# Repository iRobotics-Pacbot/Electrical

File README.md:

View this project on [CADLAB.io](https://cadlab.io/project/28443). 

﻿# Electrical

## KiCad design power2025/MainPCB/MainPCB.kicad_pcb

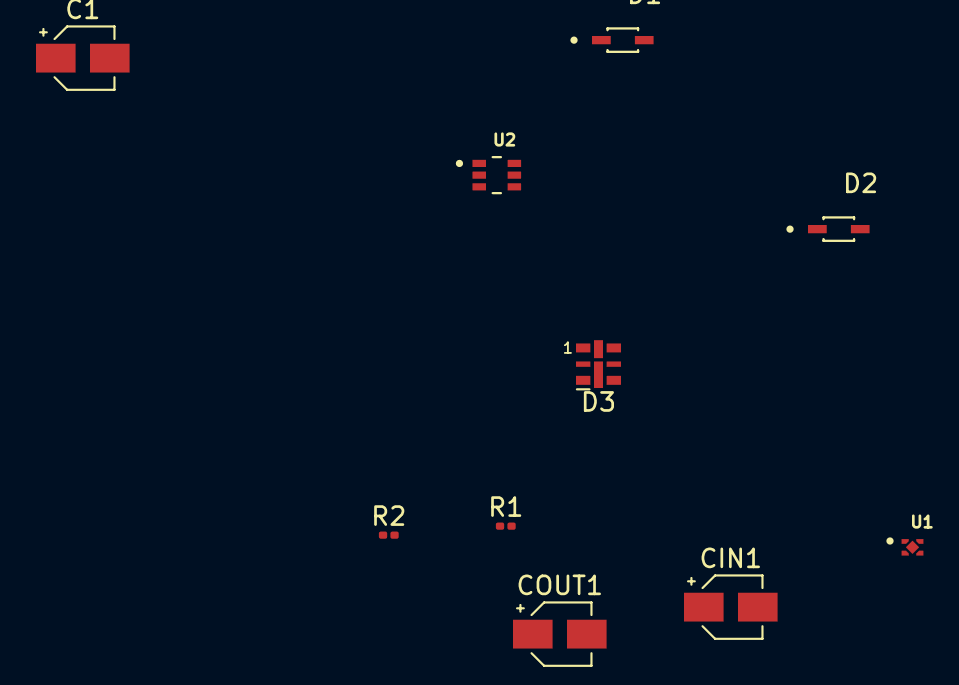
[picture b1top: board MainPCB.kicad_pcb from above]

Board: 2 copper layers, 10 parts (0 on the bottom side), 5 nets, no tracks yet.

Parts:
C1: 10uF; CP_Elec_3x5.3
CIN1: 1uF; CP_Elec_3x5.3
COUT1: 1uF; CP_Elec_3x5.3
D1, D2: D_Schottky_Filled; SOD2513X120N
D3: RED; LED-APA102-2020
R1: 100K; R_0201_0603Metric
R2: 3K3; R_0201_0603Metric
U1: NCP167BMX330TBG; VREG_NCP167BMX330TBG
U2: CJ3139K; SOP65P210X110-6N

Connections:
GND: C1.1, CIN1.2, COUT1.2, D3.1 (K), R1.1, U1.2 (GND), U1.5 (EPAD)
unnamed: C1.2, D1.1 (K), D2.2 (A), R1.2, R2.2
unnamed: CIN1.1, D2.1 (K), U1.3 (EN), U1.4 (IN)
unnamed: D3.2 (A), R2.1
unnamed: COUT1.1, U1.1 (OUT)

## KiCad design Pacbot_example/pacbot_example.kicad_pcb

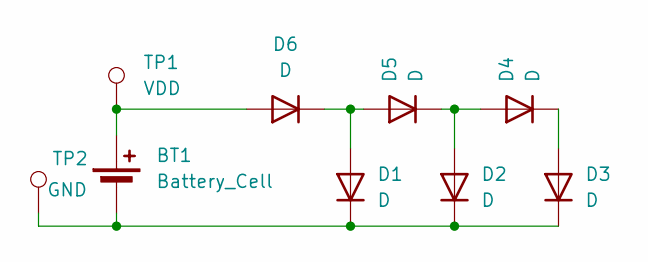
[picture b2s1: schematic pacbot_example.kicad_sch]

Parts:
BT1: Battery_Cell; BatteryHolder_LINX_BAT-HLD-012-SMT
D1, D2, D3, D4, D5, D6: D; D_0805_2012Metric
TP1: VDD; PinHeader_1x01_P2.54mm_Vertical
TP2: GND; PinHeader_1x01_P2.54mm_Vertical

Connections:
unnamed: BT1.1 (+), D6.2 (A), TP1.1
unnamed: BT1.2 (-), D1.1 (K), D2.1 (K), D3.1 (K), TP2.1
unnamed: D1.2 (A), D5.2 (A), D6.1 (K)
unnamed: D2.2 (A), D4.2 (A), D5.1 (K)
unnamed: D3.2 (A), D4.1 (K)

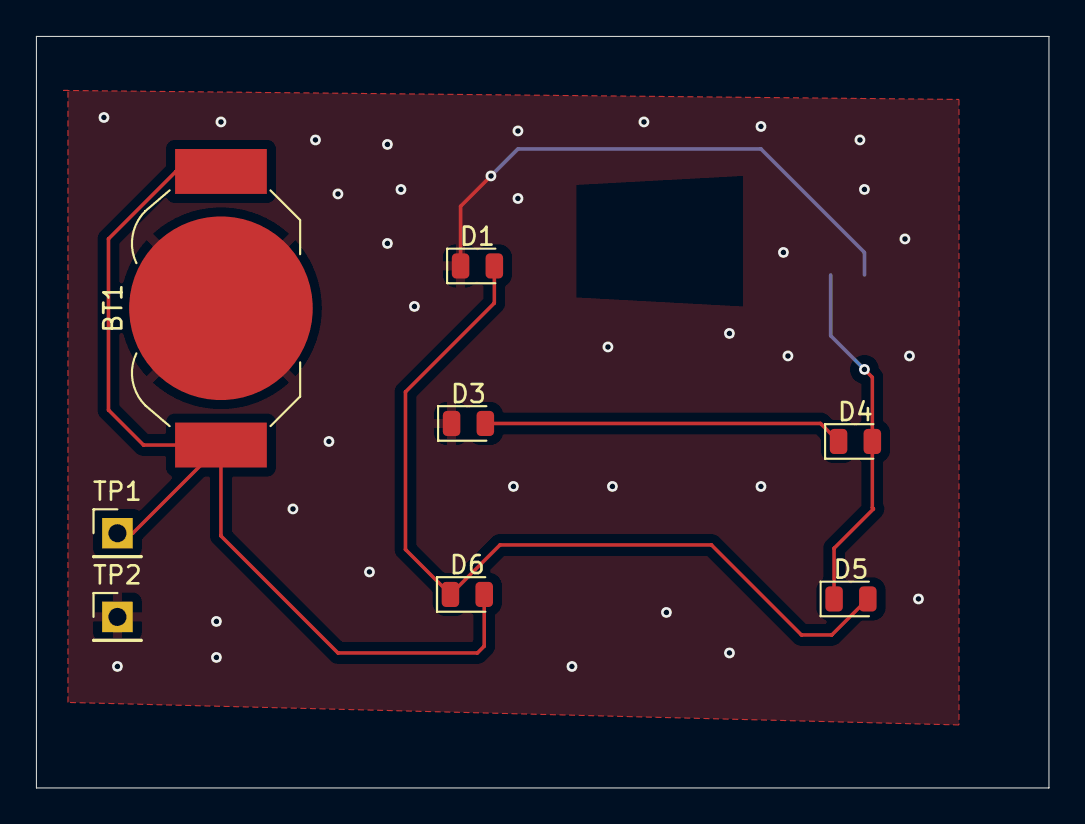
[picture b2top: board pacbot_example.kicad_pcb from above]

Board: 2 copper layers, 56.2 x 41.8 mm, 9 parts (1 on the bottom side), 5 nets.

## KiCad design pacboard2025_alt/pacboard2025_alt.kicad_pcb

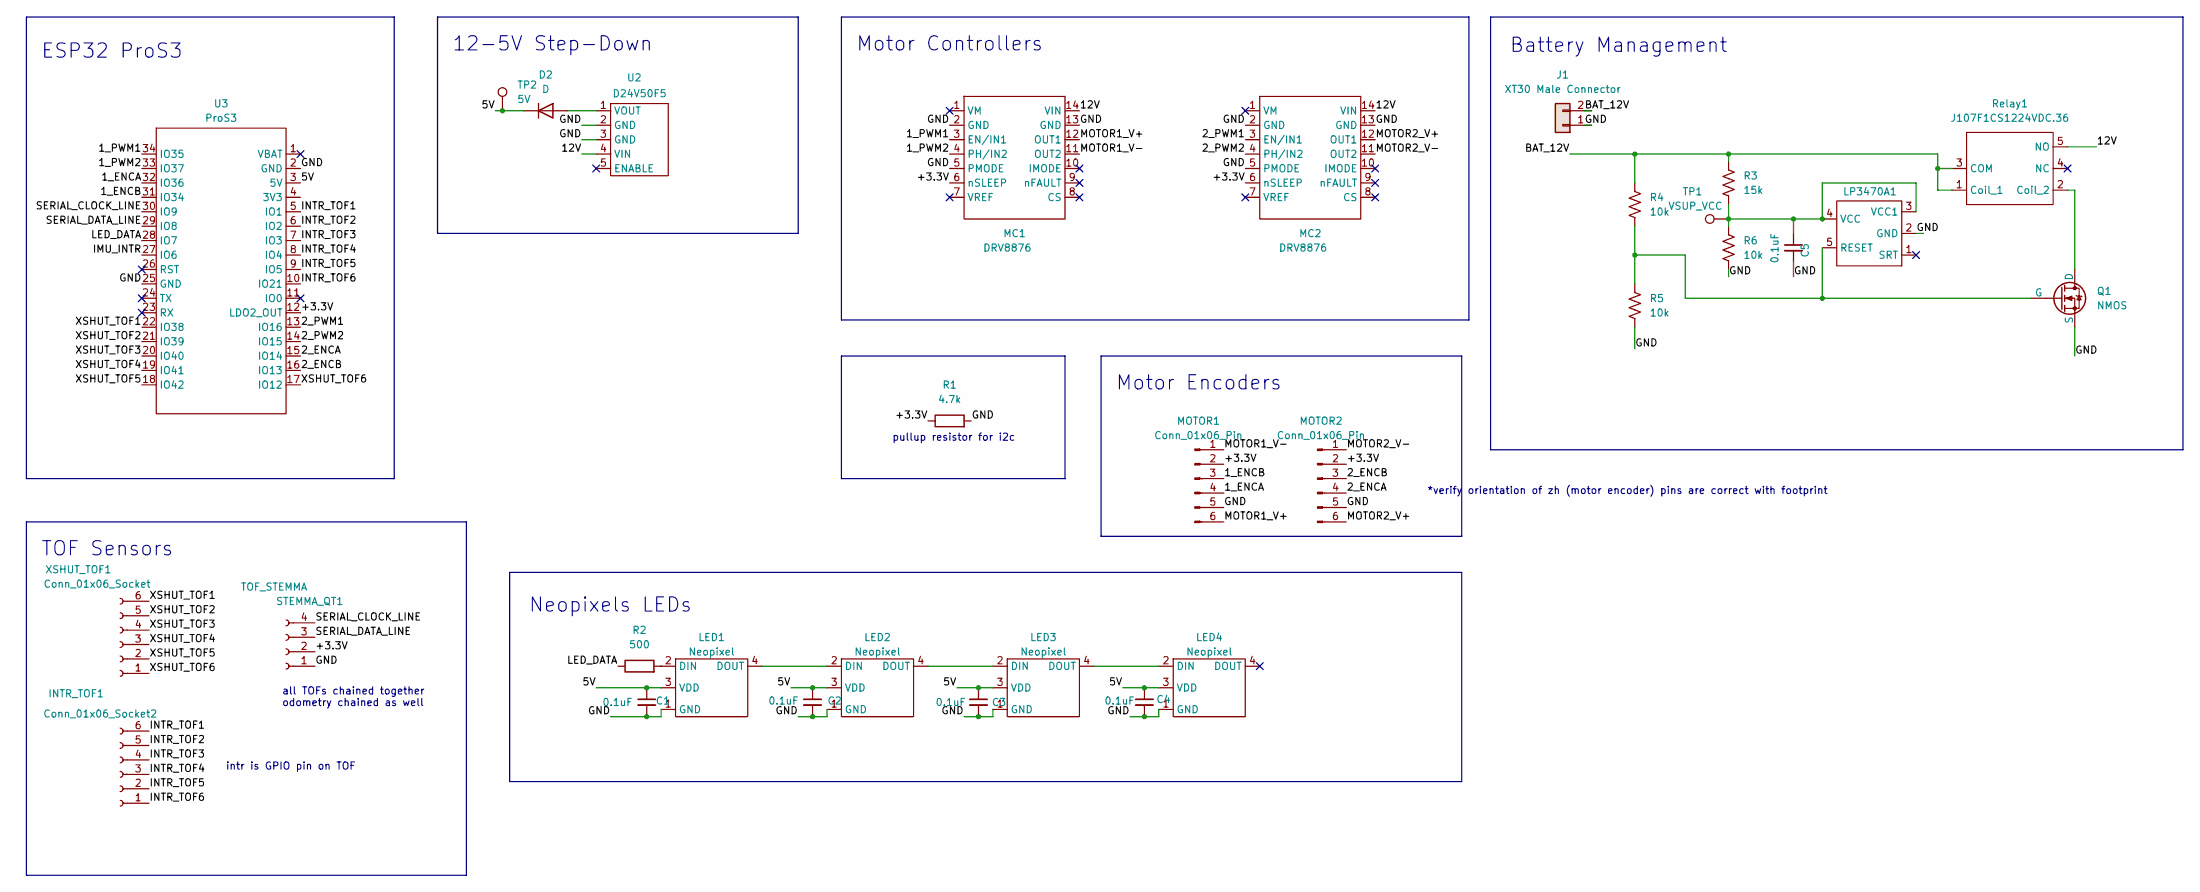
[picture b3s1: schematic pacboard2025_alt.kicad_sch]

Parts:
C1, C2, C3, C4, C5: 0.1uF; C_0805_2012Metric_Pad1.18x1.45mm_HandSolder
D2: D; D_SMB
INTR_TOF1: Conn_01x06_Socket2; PinHeader_1x06_P2.54mm_Vertical
J1: XT30 Male Connector; AMASS_XT30U-M_1x02_P5.0mm_Vertical
LED1, LED2, LED3, LED4: Neopixel; Neopixels 5050
LP3470A1: SOT-23-5
MC1, MC2: DRV8876
MOTOR1, MOTOR2: Conn_01x06_Pin; ZH1.5-6
Q1: NMOS; SOT-23
R1: 4.7k; R_0805_2012Metric_Pad1.20x1.40mm_HandSolder
R2: 500; R_0805_2012Metric_Pad1.20x1.40mm_HandSolder
R3: 15k; R_0805_2012Metric
R4, R5, R6: 10k; R_0805_2012Metric
Relay1: J107F1CS1224VDC.36; J107
STEMMA_QT1: TOF_STEMMA; JST_SH_SM04B-SRSS-TB_1x04-1MP_P1.00mm_Horizontal
TP1: VSUP_VCC; PinHeader_1x01_P2.54mm_Vertical
TP2: 5V; PinHeader_1x01_P2.54mm_Vertical
U2: D24V50F5; PinHeader_1x05_P2.54mm_Vertical
U3: ProS3; ProS3_TH (1)
XSHUT_TOF1: Conn_01x06_Socket; PinHeader_1x06_P2.54mm_Vertical

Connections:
/1_ENCA: MOTOR1.4, U3.32 (IO36)
/1_ENCB: MOTOR1.3, U3.31 (IO34)
/1_PWM1: MC1.3 (EN/IN1), U3.34 (IO35)
/1_PWM2: MC1.4 (PH/IN2), U3.33 (IO37)
/2_ENCA: MOTOR2.4, U3.15 (IO14)
/2_ENCB: MOTOR2.3, U3.16 (IO13)
/2_PWM1: MC2.3 (EN/IN1), U3.13 (IO16)
/2_PWM2: MC2.4 (PH/IN2), U3.14 (IO15)
/5V: C1.1, C2.1, C3.1, C4.1, D2.1 (K), LED1.3 (VDD), LED2.3 (VDD), LED3.3 (VDD), LED4.3 (VDD), TP2.1, U3.3 (5V)
/12V: MC1.14 (VIN), MC2.14 (VIN), Relay1.5 (NO), U2.4 (VIN)
/+3.3V: MC1.6 (nSLEEP), MC2.6 (nSLEEP), MOTOR1.2, MOTOR2.2, R1.1, STEMMA_QT1.2, U3.12 (LDO2_OUT)
/BAT_12V: J1.2, R3.1, R4.1, Relay1.1 (Coil_1), Relay1.3 (COM)
/GND: C1.2, C2.2, C3.2, C4.2, C5.2, J1.1, LED1.1 (GND), LED2.1 (GND), LED3.1 (GND), LED4.1 (GND), LP3470A1.2 (GND), MC1.2 (GND), MC1.5 (PMODE), MC1.13 (GND), MC2.2 (GND), MC2.5 (PMODE), MC2.13 (GND), MOTOR1.5, MOTOR2.5, Q1.2 (S), R1.2, R5.2, R6.2, STEMMA_QT1.1, U2.2 (GND), U2.3 (GND), U3.2 (GND), U3.25 (GND); also elsewhere on the board
/IMU_INTR: U3.27 (IO6)
/INTR_TOF1: INTR_TOF1.6, U3.5 (IO1)
/INTR_TOF2: INTR_TOF1.5, U3.6 (IO2)
/INTR_TOF3: INTR_TOF1.4, U3.7 (IO3)
/INTR_TOF4: INTR_TOF1.3, U3.8 (IO4)
/INTR_TOF5: INTR_TOF1.2, U3.9 (IO5)
/INTR_TOF6: INTR_TOF1.1, U3.10 (IO21)
/LED_DATA: R2.1, U3.28 (IO7)
/MOTOR1_V+: MC1.12 (OUT1), MOTOR1.6
/MOTOR1_V-: MC1.11 (OUT2), MOTOR1.1
/MOTOR2_V+: MC2.12 (OUT1), MOTOR2.6
/MOTOR2_V-: MC2.11 (OUT2), MOTOR2.1
/SERIAL_CLOCK_LINE: STEMMA_QT1.4, U3.30 (IO9)
/SERIAL_DATA_LINE: STEMMA_QT1.3, U3.29 (IO8)
/XSHUT_TOF1: U3.22 (IO38), XSHUT_TOF1.6
/XSHUT_TOF2: U3.21 (IO39), XSHUT_TOF1.5
/XSHUT_TOF3: U3.20 (IO40), XSHUT_TOF1.4
/XSHUT_TOF4: U3.19 (IO41), XSHUT_TOF1.3
/XSHUT_TOF5: U3.18 (IO42), XSHUT_TOF1.2
/XSHUT_TOF6: U3.17 (IO12), XSHUT_TOF1.1
unnamed: D2.2 (A), U2.1 (VOUT)
unnamed: LED1.2 (DIN), R2.2
unnamed: LED1.4 (DOUT), LED2.2 (DIN)
unnamed: LED2.4 (DOUT), LED3.2 (DIN)
unnamed: LED3.4 (DOUT), LED4.2 (DIN)
unnamed: LP3470A1.5 (RESET), Q1.1 (G), R4.2, R5.1
unnamed: C5.1, LP3470A1.3 (VCC1), LP3470A1.4 (VCC), R3.2, R6.1, TP1.1
unnamed: Q1.3 (D), Relay1.2 (Coil_2)

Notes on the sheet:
ESP32 ProS3
pullup resistor for i2c
intr is GPIO pin on TOF
Motor Encoders
all TOFs chained together odometry chained as well
12-5V Step-Down
Battery Management
*verify orientation of zh (motor encoder) pins are correct with footprint
TOF Sensors
Motor Controllers
Neopixels LEDs

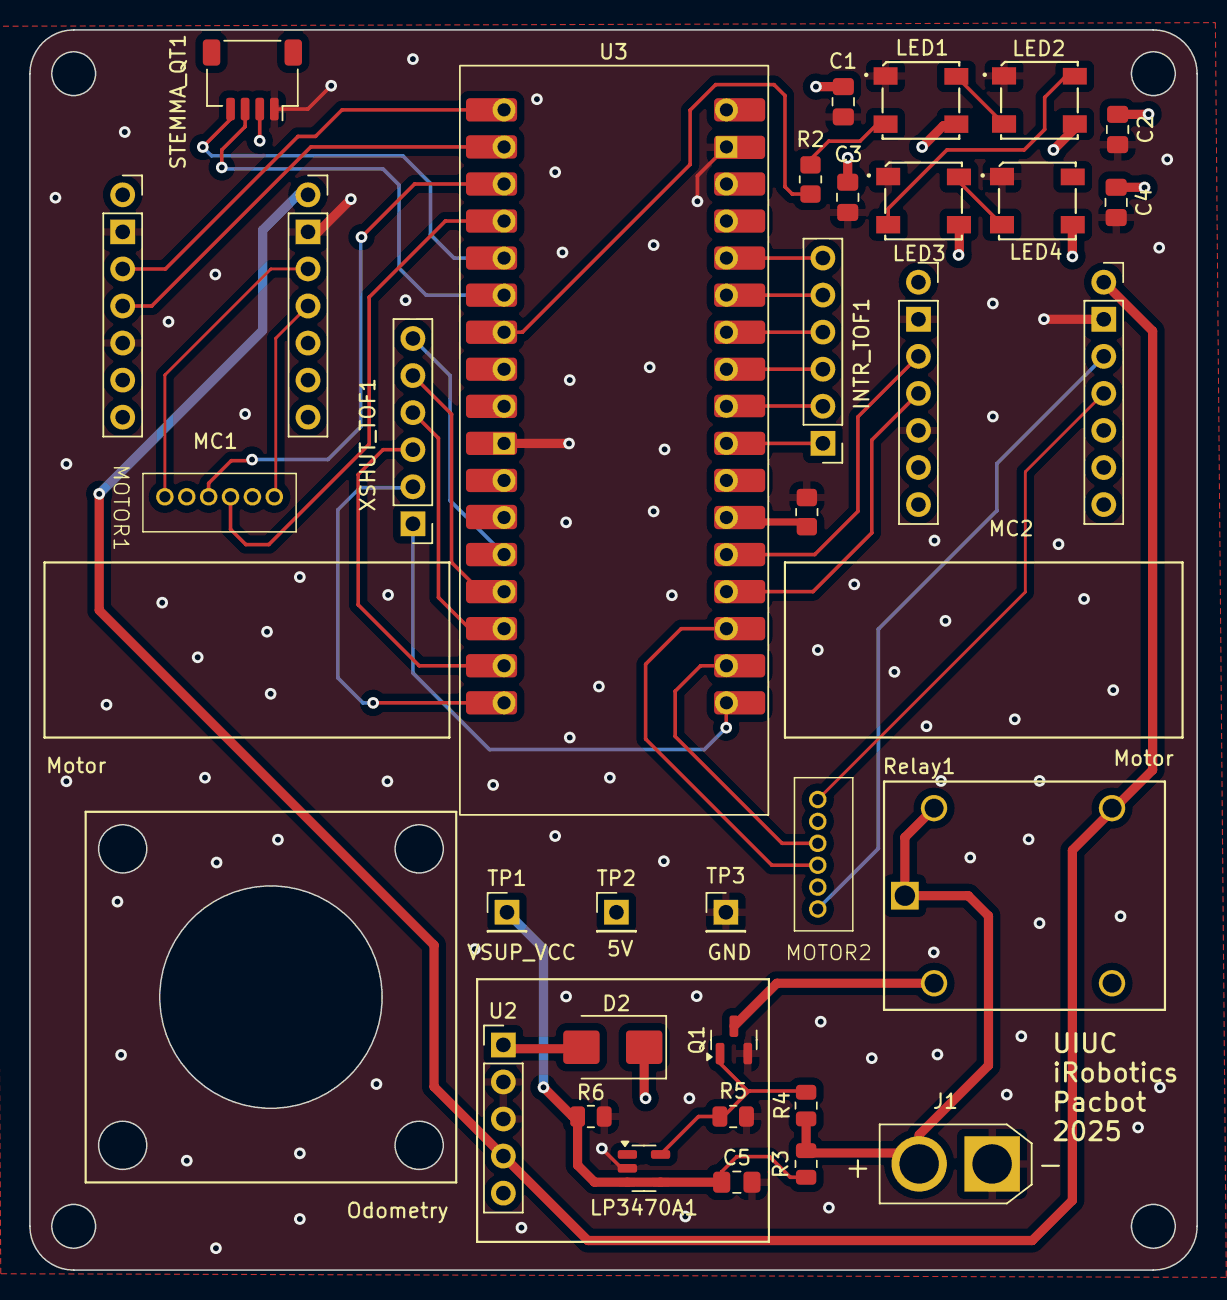
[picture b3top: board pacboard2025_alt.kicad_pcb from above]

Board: 4 copper layers, 80.0 x 85.0 mm, 32 parts (0 on the bottom side), 40 nets.

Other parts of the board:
TP3: GND; PinHeader_1x01_P2.54mm_Vertical

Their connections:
/GND: TP3.1; also elsewhere on the board

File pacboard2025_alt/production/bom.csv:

Designator,Footprint,Quantity,Value,LCSC Part #
"C1, C2, C3, C4, C5",805,5,0.1uF,C49678
D2,D_SMB,1,D,C413465
"MOTOR1, MOTOR2",ZH1.5-6,2,Conn_01x06_Pin,C722926
Q1,SOT-23,1,NMOS,C2589
R1,805,1,4.7k,C17673
R2,805,1,500,C2828711
R3,805,1,15k,C17475
"R4, R5, R6",805,3,10k,C17414
TP1,PinHeader_1x01_P2.54mm_Vertical,1,VSUP_VCC,C2906762
TP2,PinHeader_1x01_P2.54mm_Vertical,1,5V,C2906762
TP3,PinHeader_1x01_P2.54mm_Vertical,1,GND,C2906762

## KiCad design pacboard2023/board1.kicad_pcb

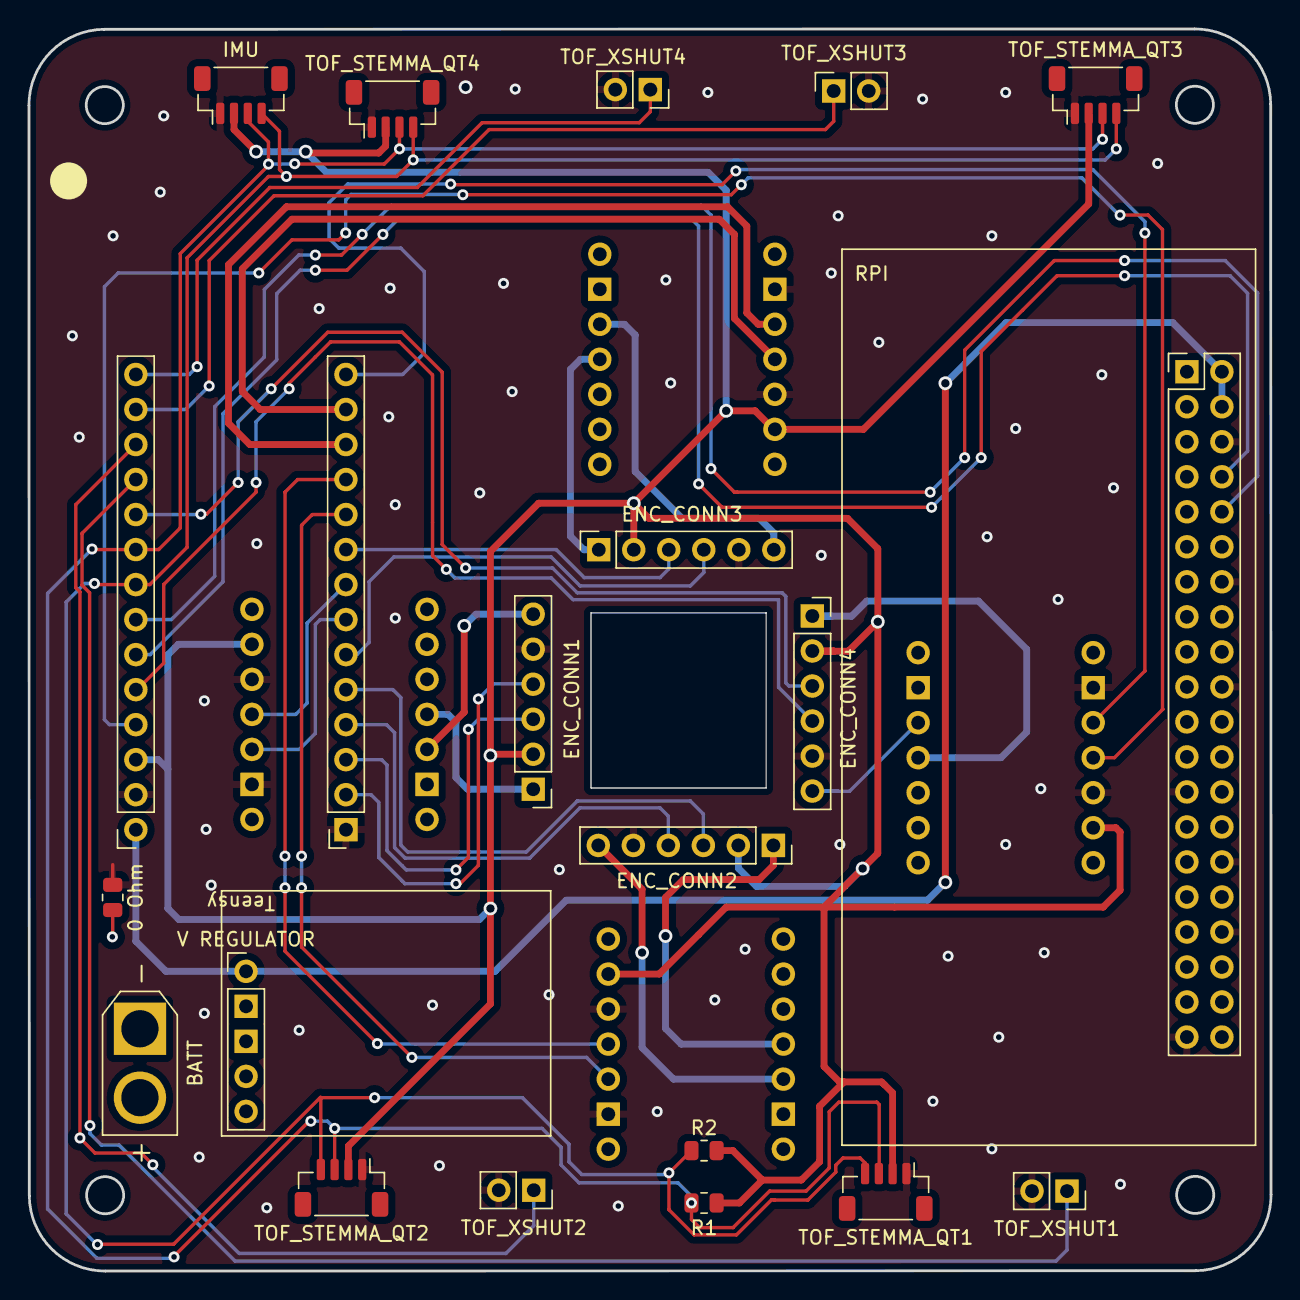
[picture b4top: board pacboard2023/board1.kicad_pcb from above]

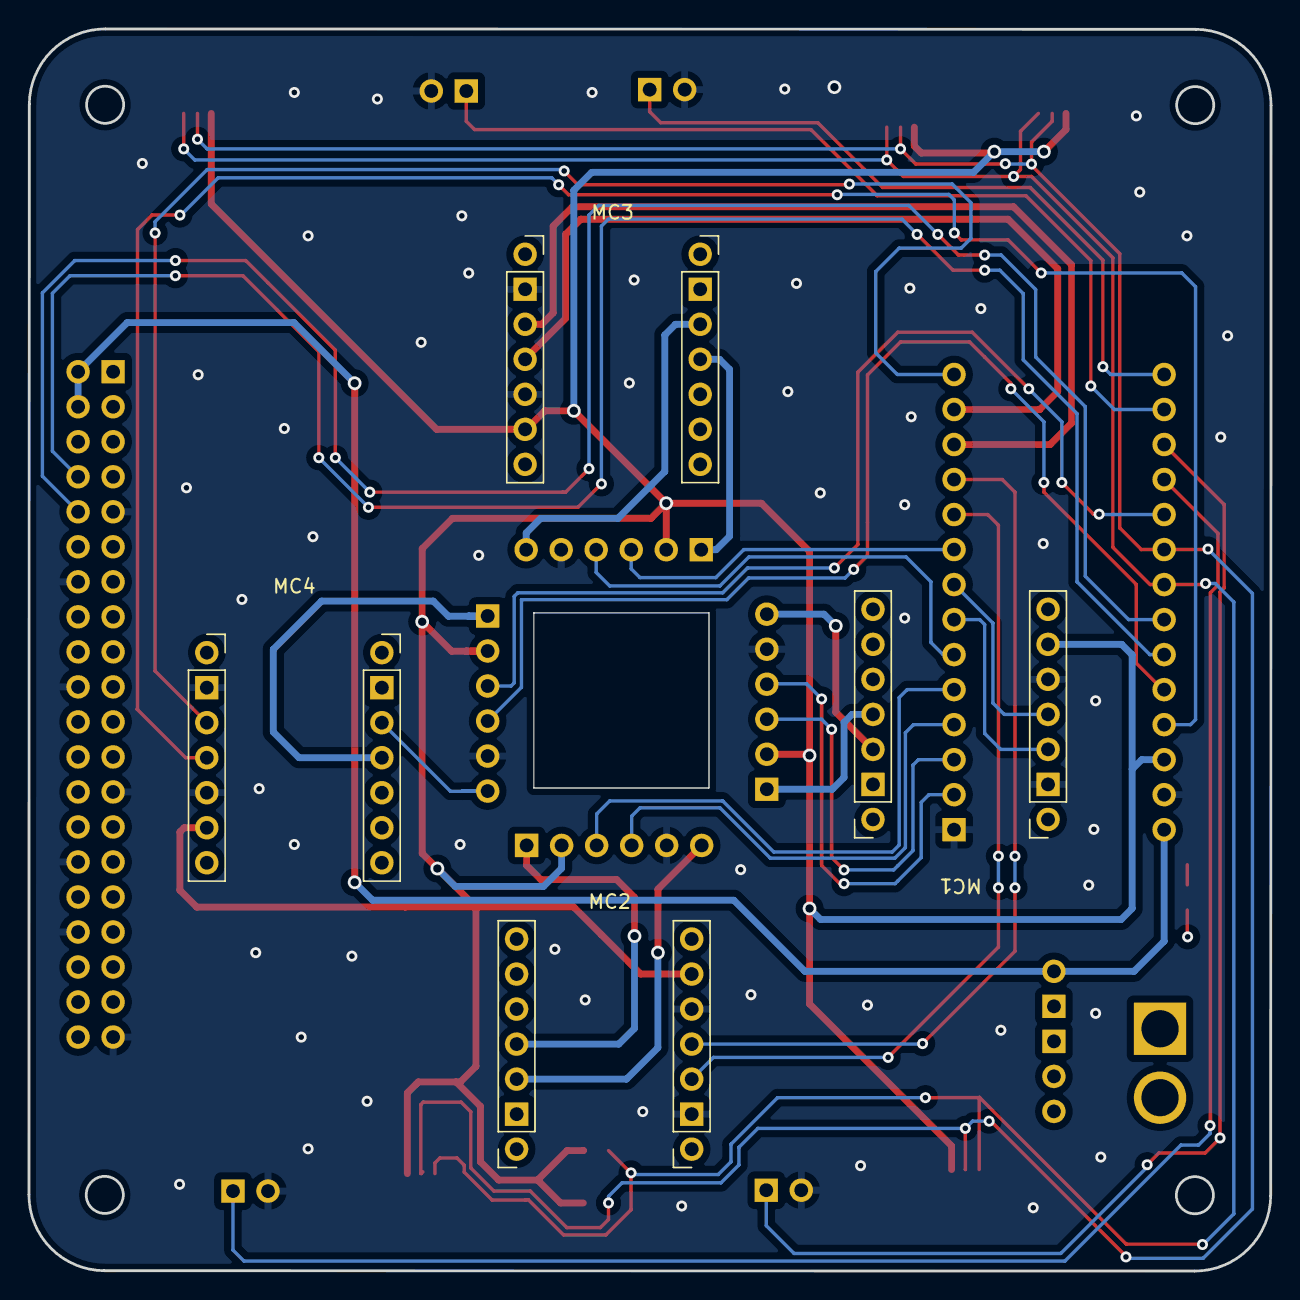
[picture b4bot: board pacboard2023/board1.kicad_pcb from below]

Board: 4 copper layers, 90.1 x 90.1 mm, 24 parts (4 on the bottom side), 37 nets.

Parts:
0 Ohm: 0 Ohms; R_0805_2012Metric
BATT: XT30 Male Connector; AMASS_XT30U-M_1x02_P5.0mm_Vertical
ENC_CONN1: Conn_01x06_Male; PinHeader_1x06_P2.54mm_Vertical
ENC_CONN2, ENC_CONN3, ENC_CONN4: Conn_01x06_Male; PinSocket_1x06_P2.54mm_Vertical
IMU: BNO085; JST_SH_BM04B-SRSS-TB_1x04-1MP_P1.00mm_Vertical
MC1, MC2, MC3, MC4: DRV8876
R1, R2: 4.7k; R_0805_2012Metric
RPI: Raspberry_PI_Zero_W; Raspberry Pi Zero W
TOF_STEMMA_QT1, TOF_STEMMA_QT2, TOF_STEMMA_QT3, TOF_STEMMA_QT4: Conn_01x04_Female; JST_SH_BM04B-SRSS-TB_1x04-1MP_P1.00mm_Vertical
TOF_XSHUT1, TOF_XSHUT2, TOF_XSHUT3, TOF_XSHUT4: Conn_01x02_Female; PinSocket_1x02_P2.54mm_Vertical
Teensy: Teensy_4.0; Teensy 4.0
V REGULATOR: D24V50F5; Voltage Regulator D24V50F5

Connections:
/3V3_Teensy: ENC_CONN1.2, ENC_CONN2.2, ENC_CONN3.2, ENC_CONN4.2, IMU.2 (VIN), MC1.6 (nSLEEP), MC2.6 (nSLEEP), MC3.6 (nSLEEP), MC4.6 (nSLEEP), R1.2, R2.2, TOF_STEMMA_QT1.2, TOF_STEMMA_QT2.2, TOF_STEMMA_QT3.2, TOF_STEMMA_QT4.2, Teensy.6 (3.3V)
/5V: RPI.2 (5V), RPI.4 (5V), Teensy.2 (Vin), V REGULATOR.1 (VOUT)
/12V: BATT.2, MC1.14 (VIN), MC2.14 (VIN), MC3.14 (VIN), MC4.14 (VIN), V REGULATOR.4 (VIN)
/BATTERY_GROUND: 0 Ohm.2, BATT.1, MC1.13 (GND), MC2.13 (GND), MC3.13 (GND), MC4.13 (GND), V REGULATOR.2 (GND), V REGULATOR.3 (GND)
/ENC_1_PINA: ENC_CONN1.4, Teensy.3 (0)
/ENC_1_PINB: ENC_CONN1.3, Teensy.5 (1)
/ENC_2_PINA: ENC_CONN2.4, Teensy.7 (2)
/ENC_2_PINB: ENC_CONN2.3, Teensy.9 (3)
/ENC_3_PINA: ENC_CONN3.4, Teensy.11 (4)
/ENC_3_PINB: ENC_CONN3.3, Teensy.17 (7)
/ENC_4_PINA: ENC_CONN4.4, Teensy.10 (22)
/ENC_4_PINB: ENC_CONN4.3, Teensy.20 (17)
/MC1_PWM1: MC1.3 (EN/IN1), Teensy.13 (5)
/MC1_PWM2: MC1.4 (PH/IN2), Teensy.15 (6)
/MC2_PWM1: MC2.3 (EN/IN1), Teensy.19 (8)
/MC2_PWM2: MC2.4 (PH/IN2), Teensy.21 (9)
/MC3_PWM1: MC3.3 (EN/IN1), Teensy.23 (10)
/MC3_PWM2: MC3.4 (PH/IN2), Teensy.25 (11)
/MC4_PWM1: MC4.3 (EN/IN1), Teensy.27 (12)
/MC4_PWM2: MC4.4 (PH/IN2), Teensy.8 (23)
/MOTOR_1_PIN1: ENC_CONN1.6, MC1.12 (OUT1)
/MOTOR_1_PIN2: ENC_CONN1.1, MC1.11 (OUT2)
/MOTOR_2_PIN1: ENC_CONN2.6, MC2.12 (OUT1)
/MOTOR_2_PIN2: ENC_CONN2.1, MC2.11 (OUT2)
/MOTOR_3_PIN1: ENC_CONN3.6, MC3.12 (OUT1)
/MOTOR_3_PIN2: ENC_CONN3.1, MC3.11 (OUT2)
/MOTOR_4_PIN1: ENC_CONN4.6, MC4.12 (OUT1)
/MOTOR_4_PIN2: ENC_CONN4.1, MC4.11 (OUT2)
/SCL_LINE: IMU.4 (SCL), R2.1, TOF_STEMMA_QT1.4, TOF_STEMMA_QT2.4, TOF_STEMMA_QT3.4, TOF_STEMMA_QT4.4, Teensy.16 (19)
/SDA_LINE: IMU.3 (SDA), R1.1, TOF_STEMMA_QT1.3, TOF_STEMMA_QT2.3, TOF_STEMMA_QT3.3, TOF_STEMMA_QT4.3, Teensy.18
/TOF_1_XSHUT: TOF_XSHUT1.1, Teensy.22 (16)
/TOF_2_XSHUT: TOF_XSHUT2.1, Teensy.24 (15)
/TOF_3_XSHUT: TOF_XSHUT3.1, Teensy.26 (14)
/TOF_4_XSHUT: TOF_XSHUT4.1, Teensy.28 (13)
/UART RXD (R PI): RPI.10 (GPIO_15_(RXD)), Teensy.14 (20)
/UART TXD (R PI): RPI.8 (GPIO_14_(TXD)), Teensy.12 (21)
GNDREF: 0 Ohm.1, ENC_CONN1.5, ENC_CONN2.5, ENC_CONN3.5, ENC_CONN4.5, IMU.1 (GND), MC1.2 (GND), MC1.5 (PMODE), MC2.2 (GND), MC2.5 (PMODE), MC3.2 (GND), MC3.5 (PMODE), MC4.2 (GND), MC4.5 (PMODE), RPI.6 (GND), RPI.9 (GND), RPI.14 (GND), RPI.20 (GND), RPI.25 (GND), RPI.30 (GND), RPI.34 (GND), RPI.39 (GND), TOF_STEMMA_QT1.1, TOF_STEMMA_QT2.1, TOF_STEMMA_QT3.1, TOF_STEMMA_QT4.1, TOF_XSHUT1.2, TOF_XSHUT2.2, TOF_XSHUT3.2, TOF_XSHUT4.2, Teensy.1 (GND), Teensy.4 (GND)

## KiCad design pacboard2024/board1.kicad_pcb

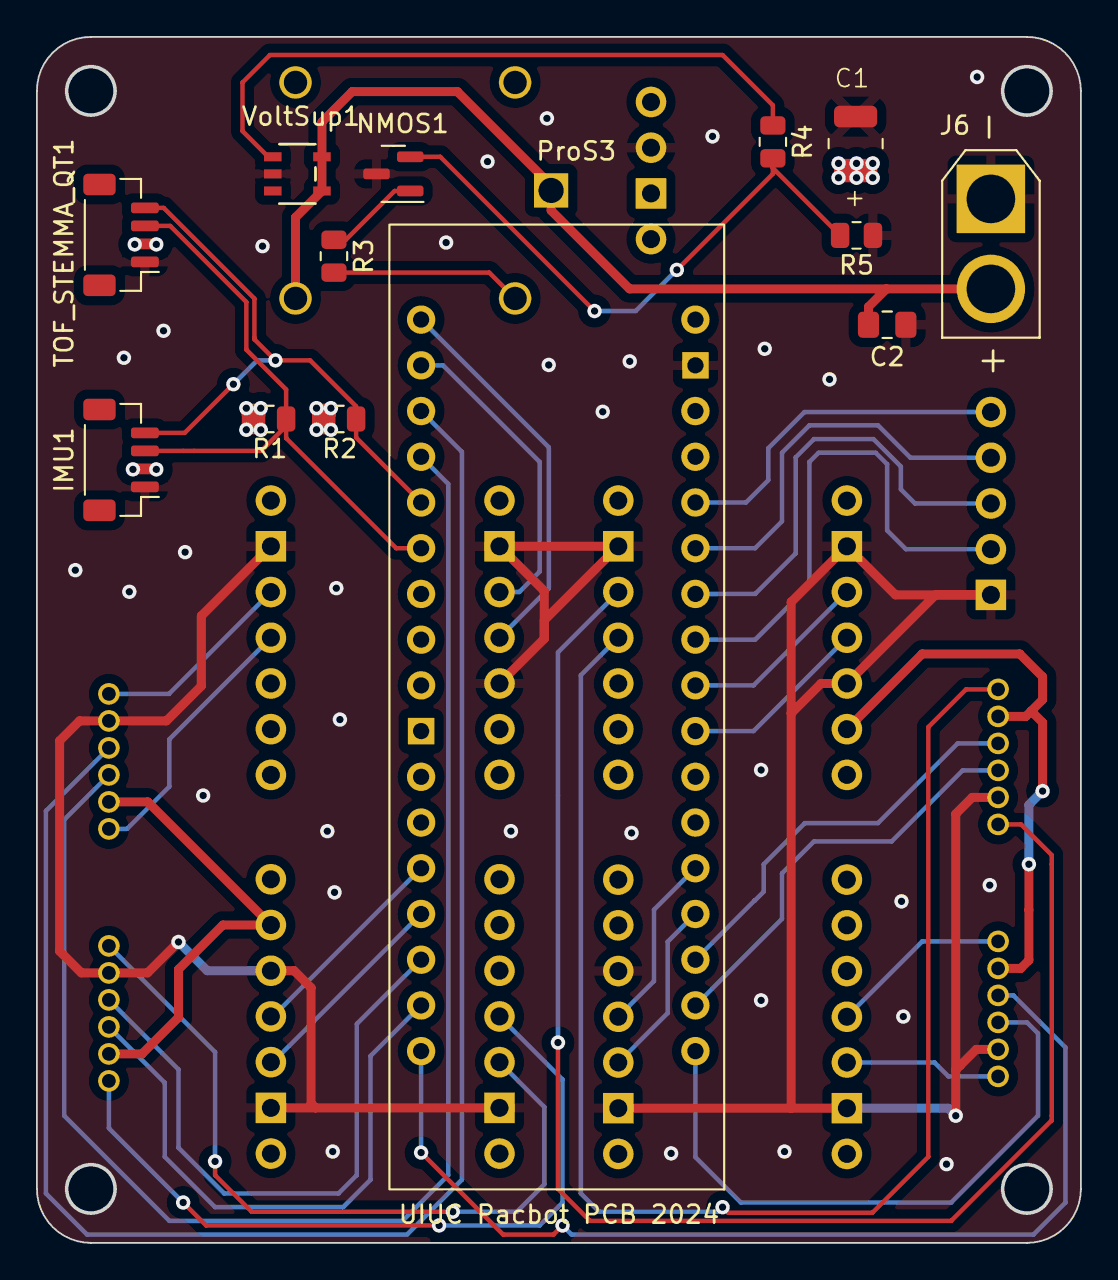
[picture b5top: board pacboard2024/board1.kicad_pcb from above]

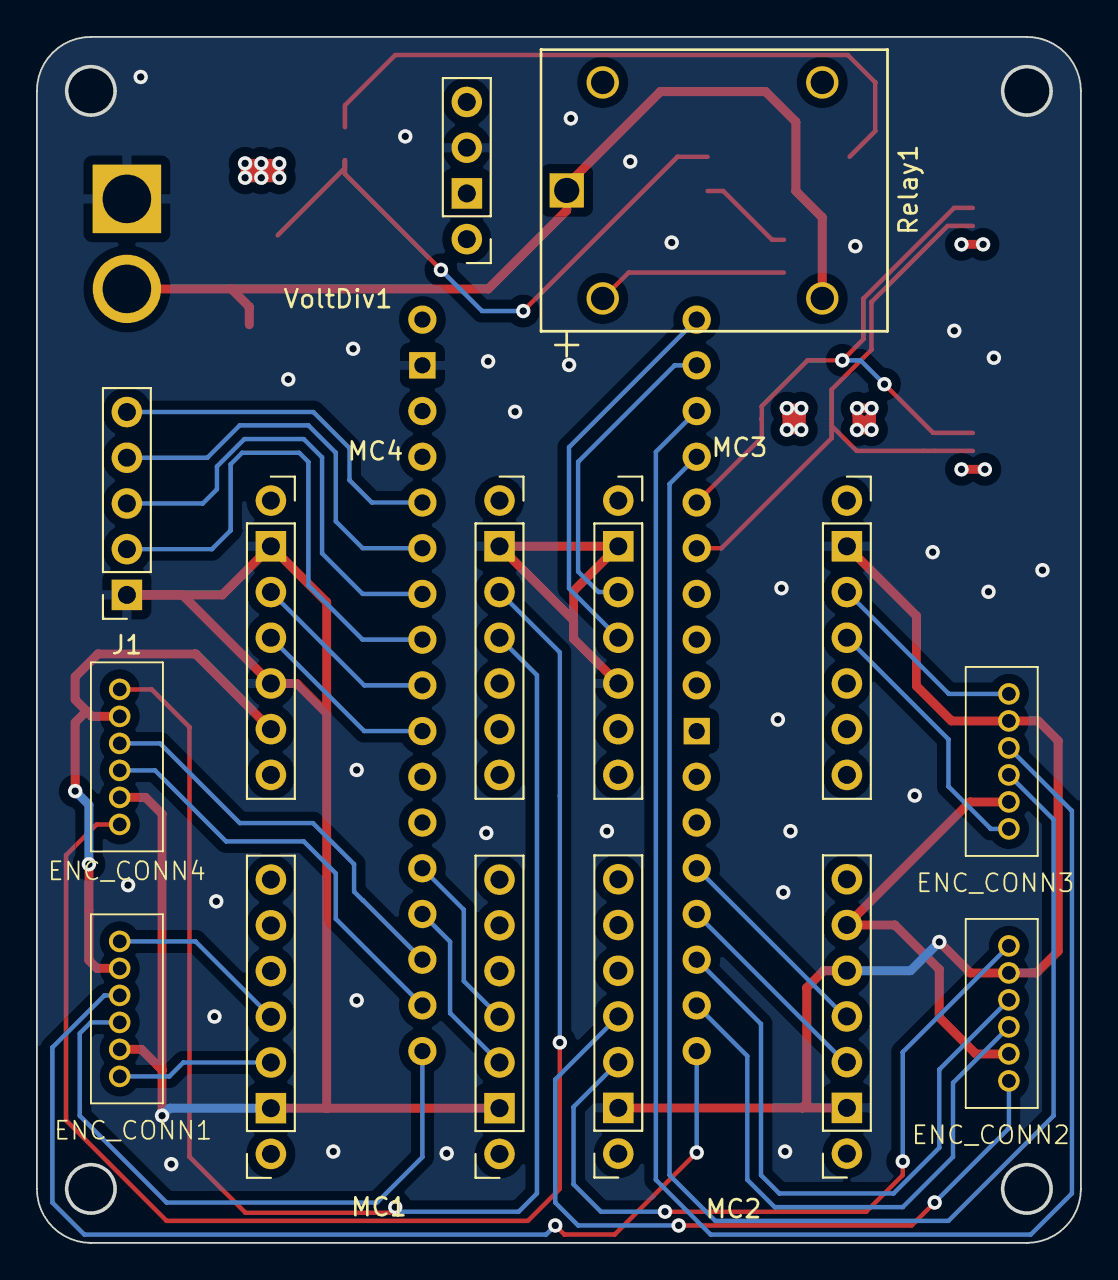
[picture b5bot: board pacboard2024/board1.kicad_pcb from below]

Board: 4 copper layers, 58.0 x 67.0 mm, 24 parts (11 on the bottom side), 38 nets.

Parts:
C1: 33uF; CA45-B-16V-33uF-K
C2: 0.1uF; C_0805_2012Metric_Pad1.18x1.45mm_HandSolder
ENC_CONN1, ENC_CONN2, ENC_CONN3, ENC_CONN4: Conn_01x06_Male; ZH1.5-6
IMU1: BNO085; JST_SH_BM04B-SRSS-TB_1x04-1MP_P1.00mm_Vertical
J1: Conn_01x05_Female; PinSocket_1x05_P2.54mm_Vertical
J6: XT30 Male Connector; AMASS_XT30U-M_1x02_P5.0mm_Vertical
MC1, MC2, MC3, MC4: DRV8876
NMOS1: Q_NMOS_DGS; SOT-23
ProS3: ProS3; ProS3_TH (1)
R1, R2: 4.7k; R_0805_2012Metric
R3: 0 Ohms; R_0805_2012Metric
R4: 1K Ohms; R_0805_2012Metric
R5: 100K Ohms; R_0805_2012Metric
Relay1: J107F1CS1224VDC.36; J107
TOF_STEMMA_QT1: Conn_01x04_Female; JST_SH_BM04B-SRSS-TB_1x04-1MP_P1.00mm_Vertical
VoltDiv1: S7V8F3
VoltSup1: TPS3847085DBVR; DBV5_TEX

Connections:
/3V3: ENC_CONN1.2, ENC_CONN2.2, ENC_CONN3.2, ENC_CONN4.2, IMU1.2 (VIN), MC1.6 (nSLEEP), MC2.6 (nSLEEP), MC3.6 (nSLEEP), MC4.6 (nSLEEP), ProS3.1 (VBAT), R1.2, R2.2, TOF_STEMMA_QT1.2, VoltDiv1.4 (VOUT)
/12V: C1.1, MC1.14 (VIN), MC2.14 (VIN), MC3.14 (VIN), MC4.14 (VIN), Relay1.5 (NO), VoltDiv1.2 (VIN)
/ENC_1_PINA: ENC_CONN1.4, ProS3.17 (IO12)
/ENC_1_PINB: ENC_CONN1.3, ProS3.18 (IO42)
/ENC_2_PINA: ENC_CONN2.4, ProS3.20 (IO40)
/ENC_2_PINB: ENC_CONN2.3, ProS3.19 (IO41)
/ENC_3_PINA: ENC_CONN3.4, ProS3.32 (IO36)
/ENC_3_PINB: ENC_CONN3.3, ProS3.31 (IO34)
/ENC_4_PINA: ENC_CONN4.4, ProS3.16 (IO13)
/ENC_4_PINB: ENC_CONN4.3, ProS3.15 (IO14)
/MC1_PWM1: MC1.3 (EN/IN1), ProS3.14 (IO15)
/MC1_PWM2: MC1.4 (PH/IN2), ProS3.13 (IO16)
/MC2_PWM1: MC2.3 (EN/IN1), ProS3.21 (IO39)
/MC2_PWM2: MC2.4 (PH/IN2), ProS3.22 (IO38)
/MC3_PWM1: MC3.3 (EN/IN1), ProS3.33 (IO37)
/MC3_PWM2: MC3.4 (PH/IN2), ProS3.34 (IO35)
/MC4_PWM1: MC4.3 (EN/IN1), ProS3.9 (IO5)
/MC4_PWM2: MC4.4 (PH/IN2), ProS3.10 (IO21)
/MOTOR_1_PIN1: ENC_CONN1.6, MC1.12 (OUT1)
/MOTOR_1_PIN2: ENC_CONN1.1, MC1.11 (OUT2)
/MOTOR_2_PIN1: ENC_CONN2.6, MC2.12 (OUT1)
/MOTOR_2_PIN2: ENC_CONN2.1, MC2.11 (OUT2)
/MOTOR_3_PIN1: ENC_CONN3.6, MC3.12 (OUT1)
/MOTOR_3_PIN2: ENC_CONN3.1, MC3.11 (OUT2)
/MOTOR_4_PIN1: ENC_CONN4.6, MC4.12 (OUT1)
/MOTOR_4_PIN2: ENC_CONN4.1, MC4.11 (OUT2)
/SCL_LINE: IMU1.4 (SCL), ProS3.30 (IO9), R2.1, TOF_STEMMA_QT1.4
/SDA_LINE: IMU1.3 (SDA), ProS3.29 (IO8), R1.1, TOF_STEMMA_QT1.3
/TOF_1_XSHUT: J1.5, ProS3.5 (IO1)
/TOF_2_XSHUT: J1.4, ProS3.6 (IO2)
/TOF_3_XSHUT: J1.3, ProS3.7 (IO3)
/TOF_4_XSHUT: J1.2, ProS3.8 (IO4)
GNDREF: C1.2, C2.2, ENC_CONN1.5, ENC_CONN2.5, ENC_CONN3.5, ENC_CONN4.5, IMU1.1 (GND), J1.1, J6.1, MC1.2 (GND), MC1.5 (PMODE), MC1.13 (GND), MC2.2 (GND), MC2.5 (PMODE), MC2.13 (GND), MC3.2 (GND), MC3.5 (PMODE), MC3.13 (GND), MC4.2 (GND), MC4.5 (PMODE), MC4.13 (GND), NMOS1.3 (S), ProS3.2 (GND), R5.1, TOF_STEMMA_QT1.1, VoltDiv1.3 (GND), VoltSup1.2 (GND)
unnamed: C2.1, J6.2, Relay1.1 (Coil_1), Relay1.3 (COM), VoltSup1.4 (*MR), VoltSup1.5 (VCC)
unnamed: NMOS1.1 (D), R3.1
unnamed: NMOS1.2 (G), R4.2, R5.2
unnamed: R3.2, Relay1.2 (Coil_2)
unnamed: R4.1, VoltSup1.1 (*RESET)

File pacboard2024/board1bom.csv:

"Id";"Designator";"Footprint";"Quantity";"Designation";"Supplier and ref";
1;"Relay1";"J107";1;"J107F1CS1224VDC.36";;;
2;"R5";"R_0805_2012Metric";1;"100K Ohms";;;
3;"NMOS1";"SOT-23";1;"Q_NMOS_DGS";;;
4;"R3";"R_0805_2012Metric";1;"0 Ohms";;;
5;"C1";"CA45-B-16V-33uF-K";1;"33uF";;;
6;"IMU1";"JST_SH_BM04B-SRSS-TB_1x04-1MP_P1.00mm_Vertical";1;"BNO085";;;
7;"TP-,TP+";"PinHeader_1x01_P2.54mm_Vertical";2;"TestPoint";;;
8;"R4";"R_0805_2012Metric";1;"1K Ohms";;;
9;"J6";"AMASS_XT30U-M_1x02_P5.0mm_Vertical";1;"XT30 Male Connector";;;
10;"R1,R2";"R_0805_2012Metric";2;"4.7k";;;
11;"VoltSup1";"DBV5_TEX";1;"TPS3847085DBVR";;;
12;"TOF_STEMMA_QT1";"JST_SH_BM04B-SRSS-TB_1x04-1MP_P1.00mm_Vertical";1;"Conn_01x04_Female";;;
13;"ProS3";"ProS3_TH (1)";1;"ProS3";;;
14;"C2";"C_0805_2012Metric_Pad1.18x1.45mm_HandSolder";1;"0.1uF";;;
15;"J1";"PinSocket_1x05_P2.54mm_Vertical";1;"Conn_01x05_Female";;;
16;"MC3,MC2,MC1,MC4";"DRV8876";4;"DRV8876";;;
17;"ENC_CONN2,ENC_CONN3,ENC_CONN4,ENC_CONN1";"ZH1.5-6";4;"Conn_01x06_Male";;;
18;"VoltDiv1";"S7V8F3";1;"~";;;

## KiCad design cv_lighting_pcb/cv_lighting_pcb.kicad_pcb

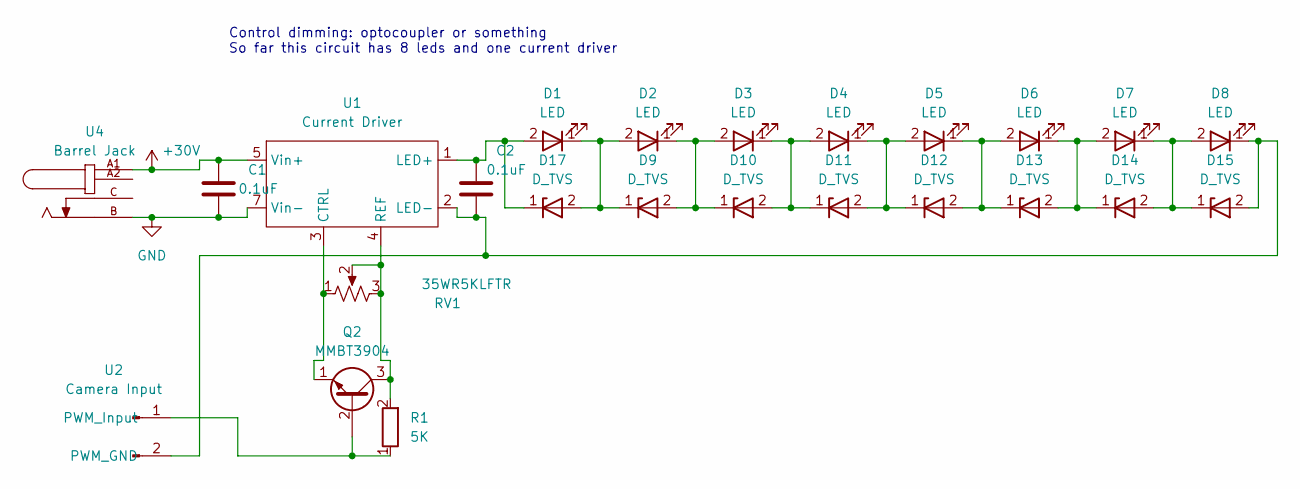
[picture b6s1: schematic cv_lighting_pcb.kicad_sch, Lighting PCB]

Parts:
C1, C2: 0.1uF; C_0805_2012Metric_Pad1.18x1.45mm_HandSolder
D1, D2, D3, D4, D5, D6, D7, D8: LED; LED_SFH4715AS
D9, D10, D11, D12, D13, D14, D15, D17: D_TVS; D3V3M1U2S9-7
Q2: MMBT3904
R1: 5K; R_0805_2012Metric_Pad1.20x1.40mm_HandSolder
RV1: 35WR5KLFTR
U1: Current Driver; 3021_Buckpuck
U2: Camera Input; PinSocket_1x02_P2.54mm_Vertical_SMD_Pin1Left
U4: Barrel Jack; TENSILITY_54-00164

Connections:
+30V: C1.1, U1.5 (Vin+), U4.A1
GND: C1.2, U1.7 (Vin-), U4.B
unnamed: C2.1, D1.2 (A), D17.1 (K), U1.1 (LED+)
unnamed: D1.1 (K), D2.2 (A), D9.1 (K), D17.2 (A)
unnamed: D3.1 (K), D4.2 (A), D10.2 (A), D11.1 (K)
unnamed: D2.1 (K), D3.2 (A), D9.2 (A), D10.1 (K)
unnamed: D4.1 (K), D5.2 (A), D11.2 (A), D12.1 (K)
unnamed: D5.1 (K), D6.2 (A), D12.2 (A), D13.1 (K)
unnamed: D6.1 (K), D7.2 (A), D13.2 (A), D14.1 (K)
unnamed: D7.1 (K), D8.2 (A), D14.2 (A), D15.1 (K)
unnamed: C2.2, D8.1 (K), D15.2 (A), U1.2 (LED-), U2.2 (PWM_GND)
unnamed: Q2.2 (B), R1.1, U2.1 (PWM_Input)
unnamed: Q2.3 (C), R1.2, RV1.2, RV1.3, U1.4 (REF)
unnamed: Q2.1 (E), RV1.1, U1.3 (CTRL)

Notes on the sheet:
Control dimming: optocoupler or something So far this circuit has 8 leds and one current driver

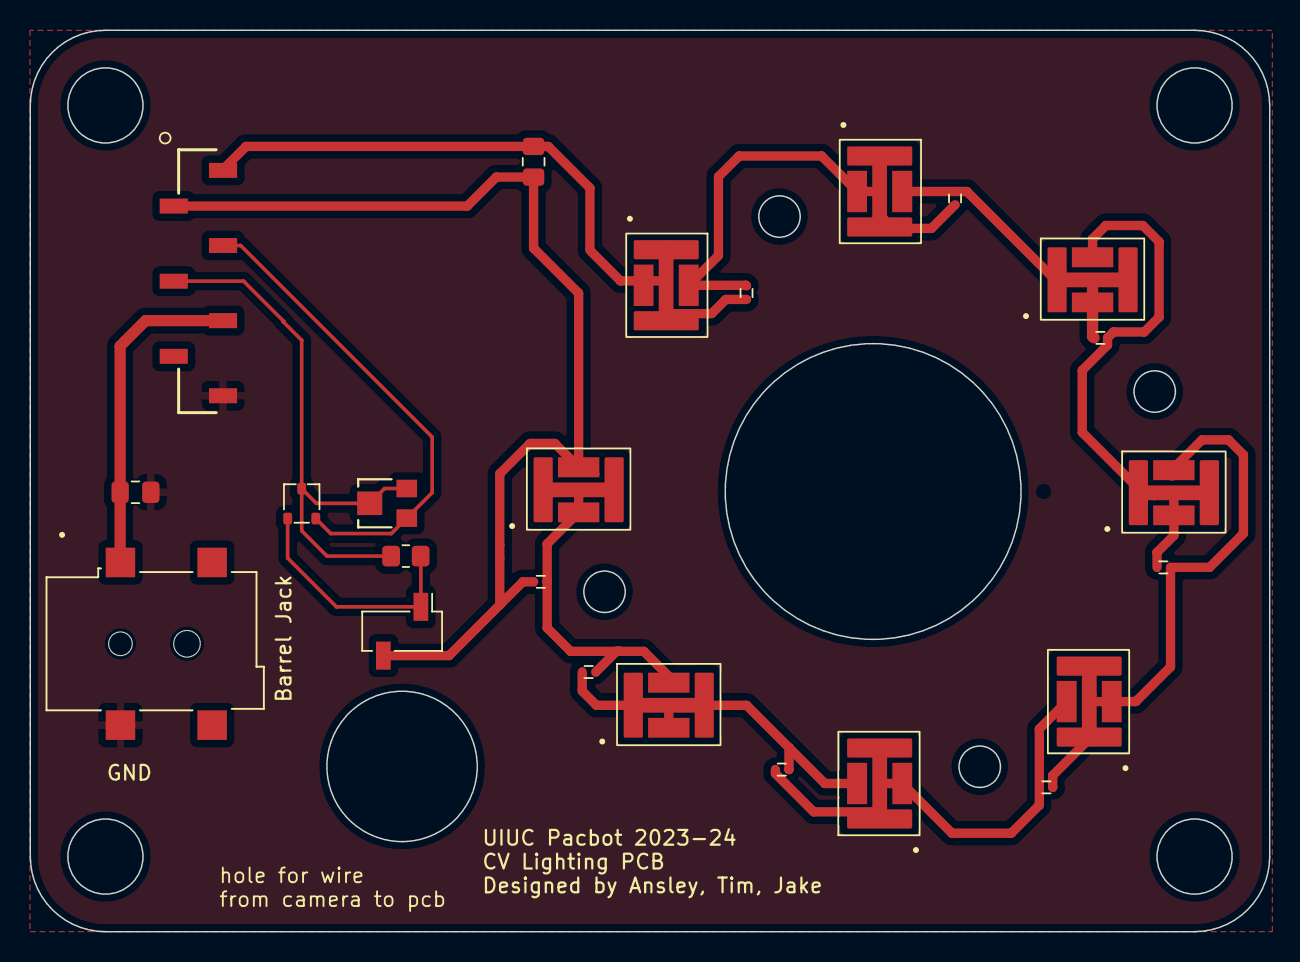
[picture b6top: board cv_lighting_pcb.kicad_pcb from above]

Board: 2 copper layers, 83.8 x 61.0 mm, 24 parts (0 on the bottom side), 14 nets.

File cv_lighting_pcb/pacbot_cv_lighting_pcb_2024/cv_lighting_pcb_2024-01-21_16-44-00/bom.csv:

Designator,Footprint,Quantity,Value,LCSC Part #
"C1, C2",0805,2,0.1uF,C49678
"D1, D2, D3, D4, D5, D6, D7, D8",LED_SFH4715AS,8,LED,C2880156
"D10, D11, D12, D13, D14, D15, D17, D9",D3V3M1U2S9-7,8,D_TVS,C1869322
Q2,MMBT3904,1,MMBT3904,C20526
R1,0805,1,5K,C17673
RV1,35WR5KLFTR,1,35WR5KLFTR,C719177
U2,PinSocket_1x02_P2.54mm_Vertical_SMD_Pin1Left,1,Camera Input,C2883799
U4,TENSILITY_54-00164,1,Barrel Jack,C521452
